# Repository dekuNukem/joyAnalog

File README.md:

# Custom circuit board for Joycon input automation

joyAnalog is a custom board with 12 analog switches and 2 12-bit DAC channels. Its main purpose is for automating Nintendo Switch Joycon inputs, and maybe TAS as well. 

joyAnalog presents itself to PC as a virtual USB serial port, so no special drivers are needed. Simply connect the button and joystick test points to the headers to allow the Joycon be controlled from a PC.

## Specs

* STM32F072C8T6 microcontroller, 16KB RAM, 64KB ROM
* 2x ADG714 SPI analog switch
* 1KB I2C EEPROM
* Automatic power switching
* User LED and button

## Header mappings

See [this PDF](datasheets/header_mapping.pdf).

## Twitch Plays Nintendo Switch

I dug up and reused a portion of my old code for TwitchPlaysPokemonX, [see here](./TwitchPlaysNintendoSwitch).

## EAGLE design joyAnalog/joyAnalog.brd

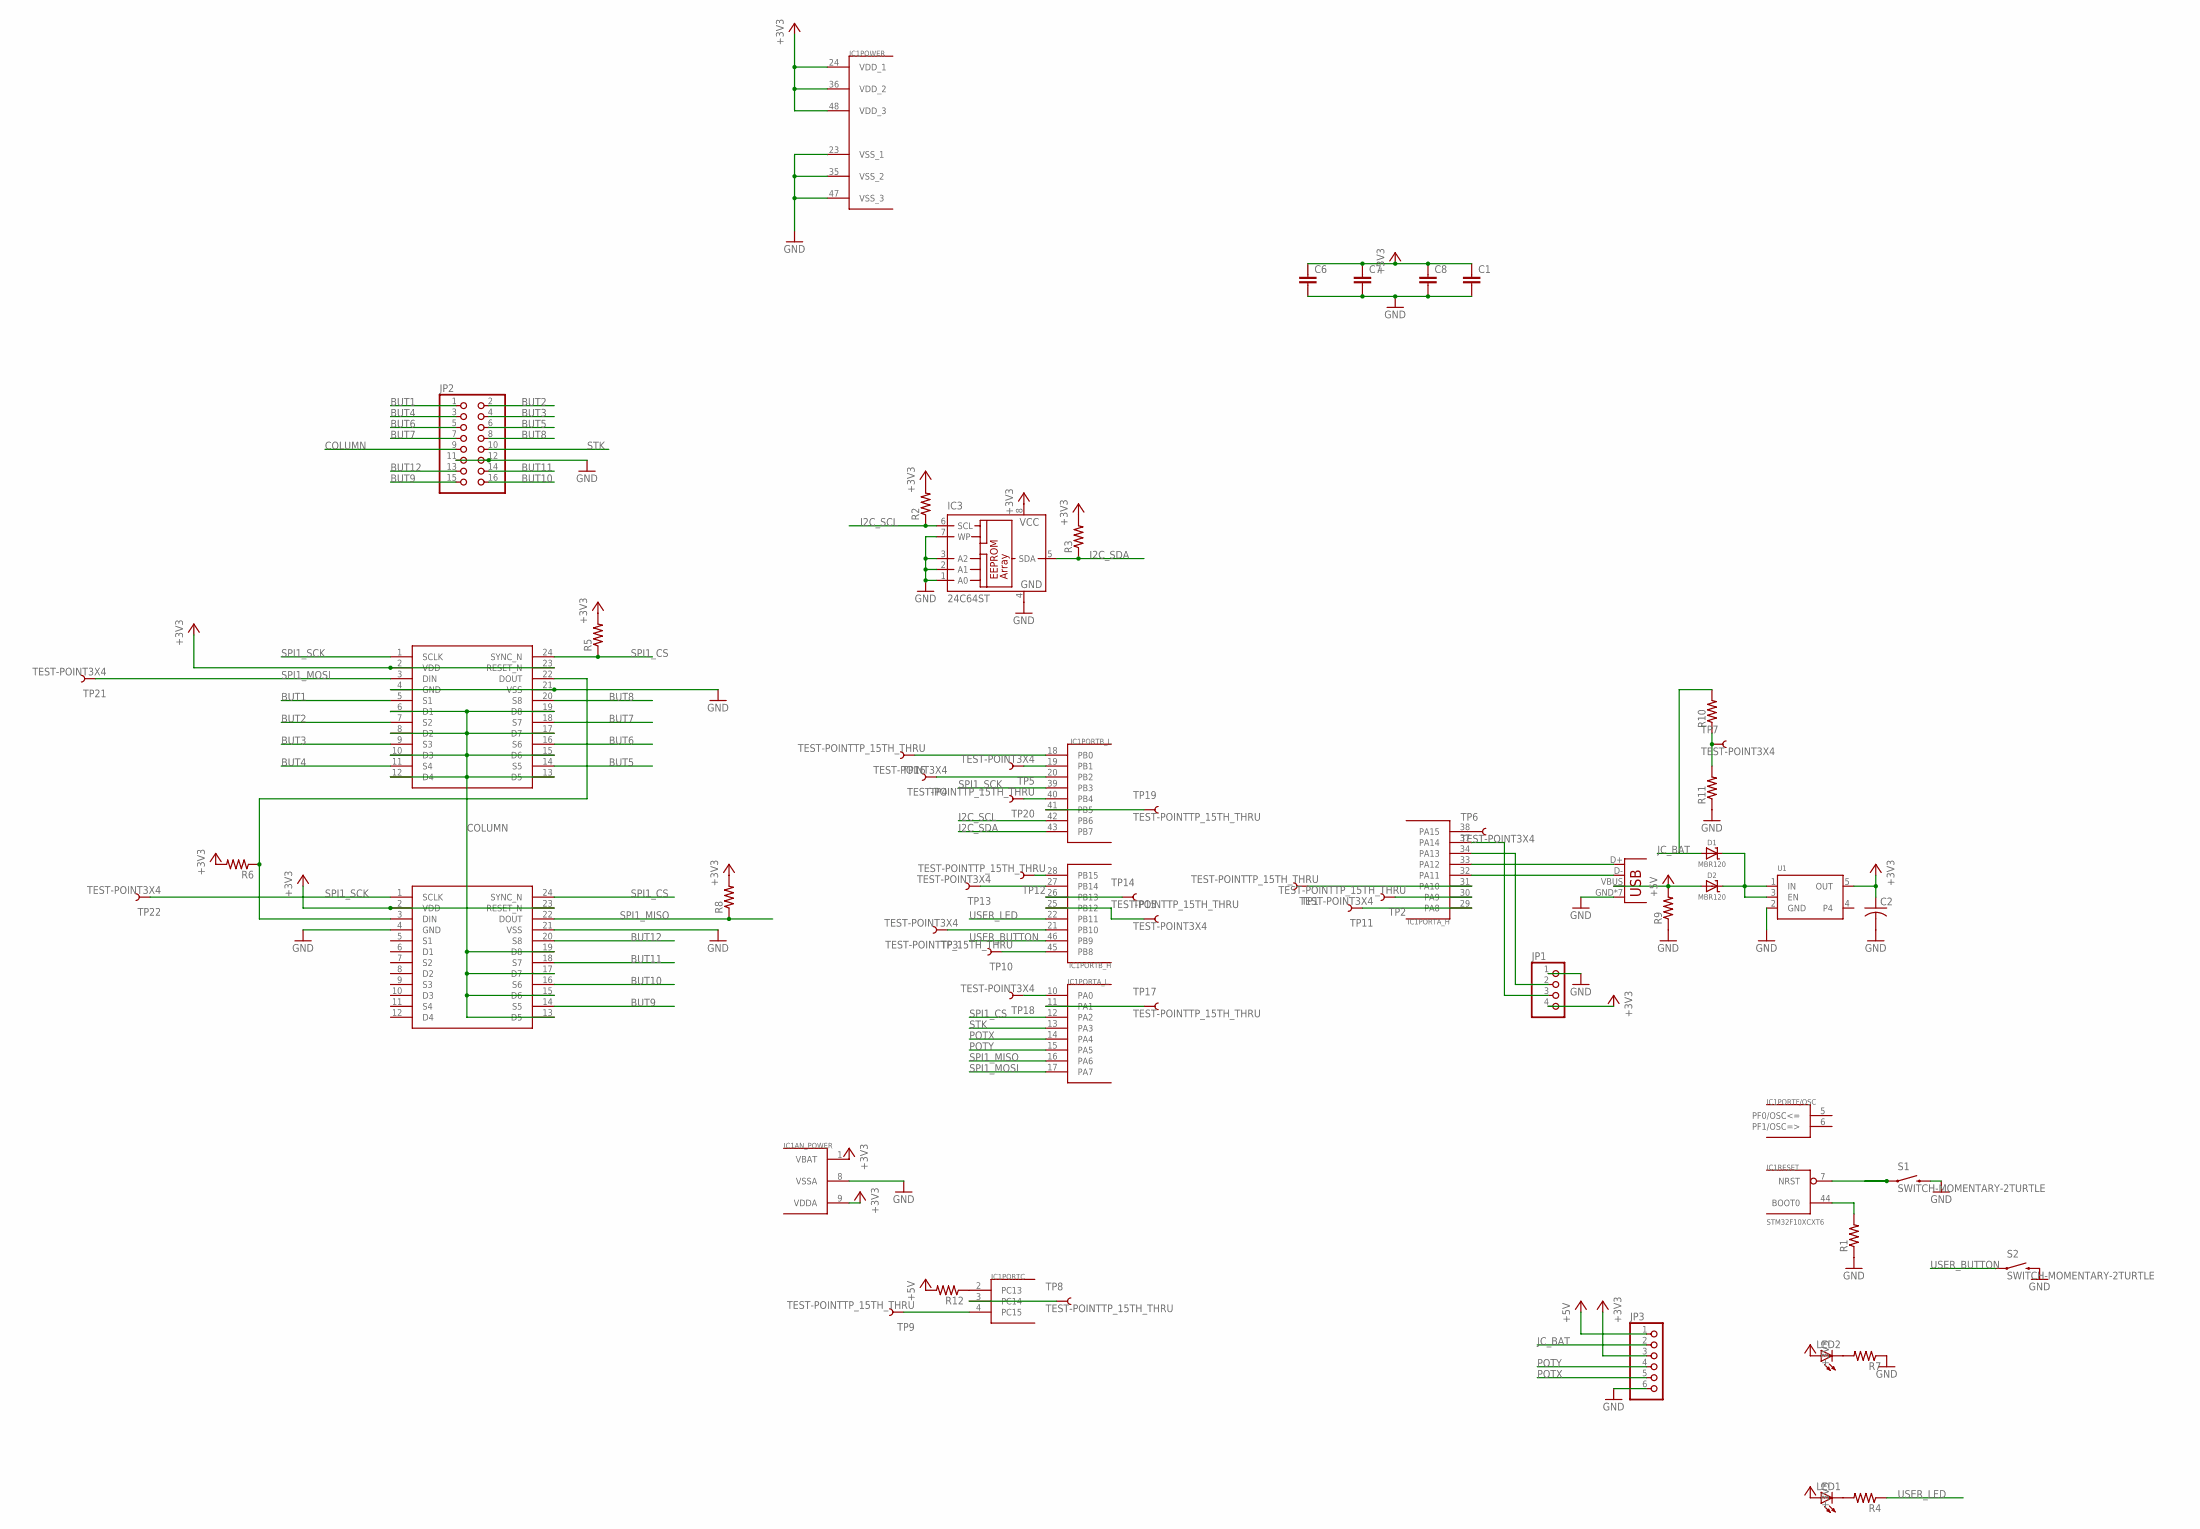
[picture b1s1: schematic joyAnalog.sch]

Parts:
C1, C6, C7, C8: CAP0805; 0805
C2: C-USC1210; C1210
D1, D2: MBR120; SOD-123
IC1: STM32F10XCXT6; TQFP48
IC3: 24C64ST; TSSOP8
JP1: PINHD-1X4; 1X04
JP2: PINHD-2X8; 2X08
JP3: PINHD-1X6CB; 1X06-CLEANBIG
LED1, LED2: LEDCHIP-LED0805; CHIP-LED0805
R1, R2, R3, R4, R5, R6, R7, R8, R9, R10, R11, R12: RESISTOR0805-RES; 0805
S1, S2: SWITCH-MOMENTARY-2TURTLE; KMR2
TP1, TP2, TP8, TP9, TP10, TP12, TP14, TP16, TP17, TP19, TP20: TEST-POINTTP_15TH_THRU; TP_15TH
TP3, TP4, TP5, TP6, TP7, TP11, TP13, TP15, TP18, TP21, TP22: TEST-POINT3X4; PAD.03X.04
U1: VREG_SOT23-5; SOT23-5
U$3, U$4: ADG714_DEV; TSSOP-24
X1: USB-MICROB

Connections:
+3V3: C1.1, C2.1, C6.1, C7.1, C8.1, IC1.1 (VBAT), IC1.9 (VDDA), IC1.24 (VDD_1), IC1.36 (VDD_2), IC1.48 (VDD_3), IC3.8 (VCC), JP1.4, JP3.3, LED1.A, LED2.A, R2.2, R3.2, R5.2, R6.2, R8.2, U1.5 (OUT), U$3.2 (VDD), U$3.23 (RESET_N), U$4.2 (VDD), U$4.23 (RESET_N)
+5V: D2.A, JP3.1, R9.2, R12.2, X1.VBUS
BUT1: JP2.1, U$3.5 (S1)
BUT2: JP2.2, U$3.7 (S2)
BUT3: JP2.4, U$3.9 (S3)
BUT4: JP2.3, U$3.11 (S4)
BUT5: JP2.6, U$3.14 (S5)
BUT6: JP2.5, U$3.16 (S6)
BUT7: JP2.7, U$3.18 (S7)
BUT8: JP2.8, U$3.20 (S8)
BUT9: JP2.15, U$4.14 (S5)
BUT10: JP2.16, U$4.16 (S6)
BUT11: JP2.14, U$4.18 (S7)
BUT12: JP2.13, U$4.20 (S8)
COLUMN: JP2.9, U$3.6 (D1), U$3.8 (D2), U$3.10 (D3), U$3.12 (D4), U$3.13 (D5), U$3.15 (D6), U$3.17 (D7), U$3.19 (D8), U$4.13 (D5), U$4.15 (D6), U$4.17 (D7), U$4.19 (D8)
GND: C1.2, C2.2, C6.2, C7.2, C8.2, IC1.8 (VSSA), IC1.23 (VSS_1), IC1.35 (VSS_2), IC1.47 (VSS_3), IC3.1 (A0), IC3.2 (A1), IC3.3 (A2), IC3.4 (GND), IC3.7 (WP), JP1.1, JP2.11, JP2.12, JP3.6, R1.1, R7.1, R9.1, R11.1, S1.3 (2), S2.3 (2), U1.2 (GND), U$3.4 (GND), U$3.21 (VSS), U$4.4 (GND), U$4.21 (VSS), X1.GND, X1.P1 (GND), X1.P2 (GND), X1.P3 (GND), X1.P4 (GND), X1.P5 (GND), X1.P6 (GND)
I2C_SCL: IC1.42 (PB6), IC3.6 (SCL), R2.1
I2C_SDA: IC1.43 (PB7), IC3.5 (SDA), R3.1
JC_BAT: D1.A, JP3.2, R10.2
unnamed: IC1.7 (NRST), S1.1
unnamed: IC1.44 (BOOT0), R1.2
unnamed: LED1.C, R4.2
unnamed: IC1.33 (PA12), X1.D+
unnamed: R6.1, U$3.22 (DOUT), U$4.3 (DIN)
unnamed: IC1.30 (PA9), TP2.P$1
unnamed: IC1.32 (PA11), X1.D-
unnamed: IC1.34 (PA13), JP1.2
unnamed: IC1.37 (PA14), JP1.3
unnamed: IC1.31 (PA10), TP1.P$1
unnamed: IC1.20 (PB2), TP4.P$1
unnamed: IC1.19 (PB1), TP5.P$1
unnamed: IC1.21 (PB10), TP3.P$1
unnamed: IC1.38 (PA15), TP6.P$1
unnamed: R10.1, R11.2, TP7.P$1
unnamed: IC1.3 (PC14), TP8.P$1
unnamed: IC1.4 (PC15), TP9.P$1
unnamed: IC1.45 (PB8), TP10.P$1
unnamed: IC1.29 (PA8), TP11.P$1
unnamed: IC1.28 (PB15), TP12.P$1
unnamed: IC1.27 (PB14), TP13.P$1
unnamed: IC1.26 (PB13), TP14.P$1
unnamed: IC1.25 (PB12), TP15.P$1
unnamed: IC1.18 (PB0), TP16.P$1
unnamed: IC1.10 (PA0), TP18.P$1
unnamed: IC1.11 (PA1), TP17.P$1
unnamed: IC1.40 (PB4), TP20.P$1
unnamed: IC1.41 (PB5), TP19.P$1
unnamed: LED2.C, R7.2
unnamed: IC1.2 (PC13), R12.1
unnamed: D1.C, D2.C, U1.1 (IN), U1.3 (EN)
POTX: IC1.14 (PA4), JP3.5
POTY: IC1.15 (PA5), JP3.4
SPI1_CS: IC1.12 (PA2), R5.1, U$3.24 (SYNC_N), U$4.24 (SYNC_N)
SPI1_MISO: IC1.16 (PA6), R8.1, U$4.22 (DOUT)
SPI1_MOSI: IC1.17 (PA7), TP21.P$1, U$3.3 (DIN)
SPI1_SCK: IC1.39 (PB3), TP22.P$1, U$3.1 (SCLK), U$4.1 (SCLK)
STK: IC1.13 (PA3), JP2.10
USER_BUTTON: IC1.46 (PB9), S2.1
USER_LED: IC1.22 (PB11), R4.1

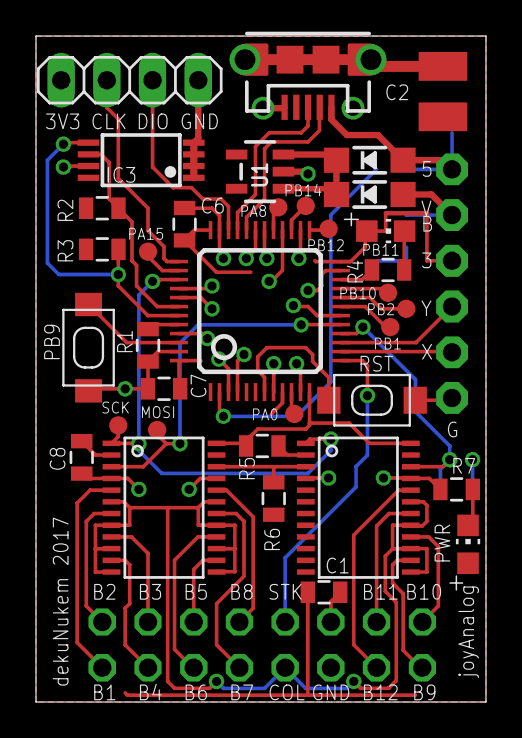
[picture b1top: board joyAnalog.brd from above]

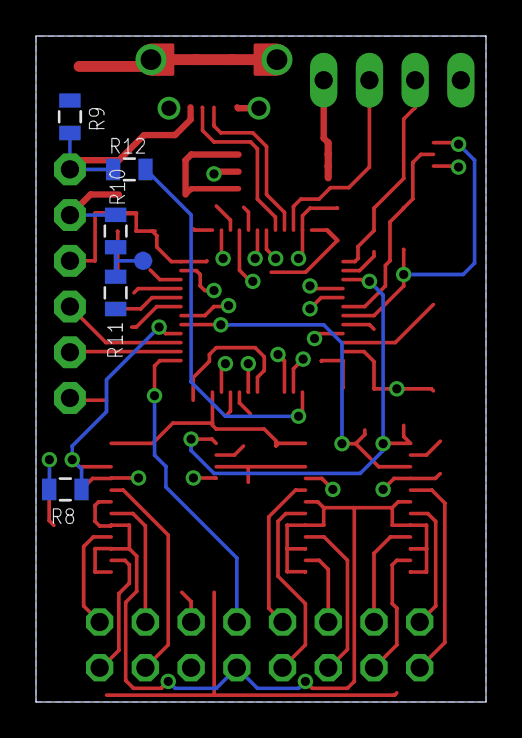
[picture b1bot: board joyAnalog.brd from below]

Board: 2 copper layers, 25.0 x 37.0 mm, 54 parts (6 on the bottom side), 59 nets.

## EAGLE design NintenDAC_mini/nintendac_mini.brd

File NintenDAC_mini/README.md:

## NintenDAC mini

This is the board that's to be used on modifying the Joycon. It's small enough to be taped to the back of each one.

* 48MHz STM32F072C8T6 microcontroller, 64KB flash, 16KB RAM.
* Built-in 2-channel 12-bit DAC.
* 1KB I2C EEPROM, user button, user LED.
* 28 GPIOs(or 32 using internal oscillators), BOOT0, RESET, VBAT, and SWD.
* USB for power and communication, standby wakeup on USB connection.
* Board size 2.5 x 4.1 cm, 1 x 1.6 inch.

## Command protocol

NintenDAC mini uses a simple serial command protocol. To use it open the port at any baud rate, then send a command in ASCII string. The board will send a response back.

Commands should be in lower case, and end with a single `\n`.

### Commands

**command**|**arguments**|**remark**|**response**|**example**
:-----:|:-----:|:-----:|:-----:|:-----:
`eepinit`|none|initializes EEPROM to default value|`eepinit OK`|`eepinit`
`settype`|l / r|set this board as left or right Joycon|`settype OK`|`settype l`
`whoami`|none|see which side is this board|A string containing `LEFT` or `RIGHT`; `unknown` if incorrectly set up|`whoami`
`bh`|button args (see below)|hold button|`bh OK` if no error; `ERROR`  otherwise|`bh a b x`
`br`|button args (see below)|release button|`br OK` if no error; `ERROR` otherwise|`br a b x`
`bra`|none|release all buttons on this board|`bra OK`|`bra`
`sh`|x y|move stick to x and y value. x y should be between 0 and 255 inclusive; 127 is netural position|`bh OK`|`sh 127 245`
`sr`|none|move stick back to netural position|`br OK`|`sr`
`sd`|none|stick disengage|`sd OK`|`sd`
`reset`|none|release all buttons as well as disengage the stick|`reset OK`|`reset`

### Button args

**arg**|**button**
:-----:|:-----:
`du`|D-pad up
`dd`|D-pad down
`dl`|D-pad left
`dr`|D-pad right
`ls`|L button
`zl`|ZL button
`-`|minus button 
`cap`|capture button
`lsl`|left Joycon SL button
`lsr`|left Joycon SR button
`syncl`|left Joycon SYNC button
`sbl`|left Joycon stick button
`a`|A button
`b`|B button
`x`|X button
`y`|Y button
`rs`|R button
`zr`|ZR button
`+`|plus button
`h`|home button
`rsl`|right Joycon SL button
`rsr`|right Joycon SR button
`syncr`|right Joycon SYNC button
`sbr`|right Joycon stick button

### A few words about commands

* `sh` and `sr` will take over the control stick, meaning the input won't change when you move the stick with your finger when those commands are active. To get back to manual control use `sd`

* Not all buttons are available on one board. For example if you try to `bh a` on a left Joycon board, you will get an error because there is no A button on left Joycon.

* `bh` and `br` can have one or multiple arguments, as long as they are all valid. So you can have `bh a` or `bh a b x y zr h +` etc. The max number of arguments is 16.

## NintenDAC Python3 library

I also wrote a [python3 library](./pythonlib) so you don't have to remember all the commands above. It requires `pyserial`.

A simple example:

```
import ndacmini

switch = ndacmini.ndacmini("COM5", "COM6")
switch.connect()

switch.button_hold(['a', 'b', 'zl', 'zr'])
switch.stick_hold('l', 64, 192)
switch.reset()
switch.disconnect()

```

A more detailed example with comments can be found [here](./pythonlib/example.py)

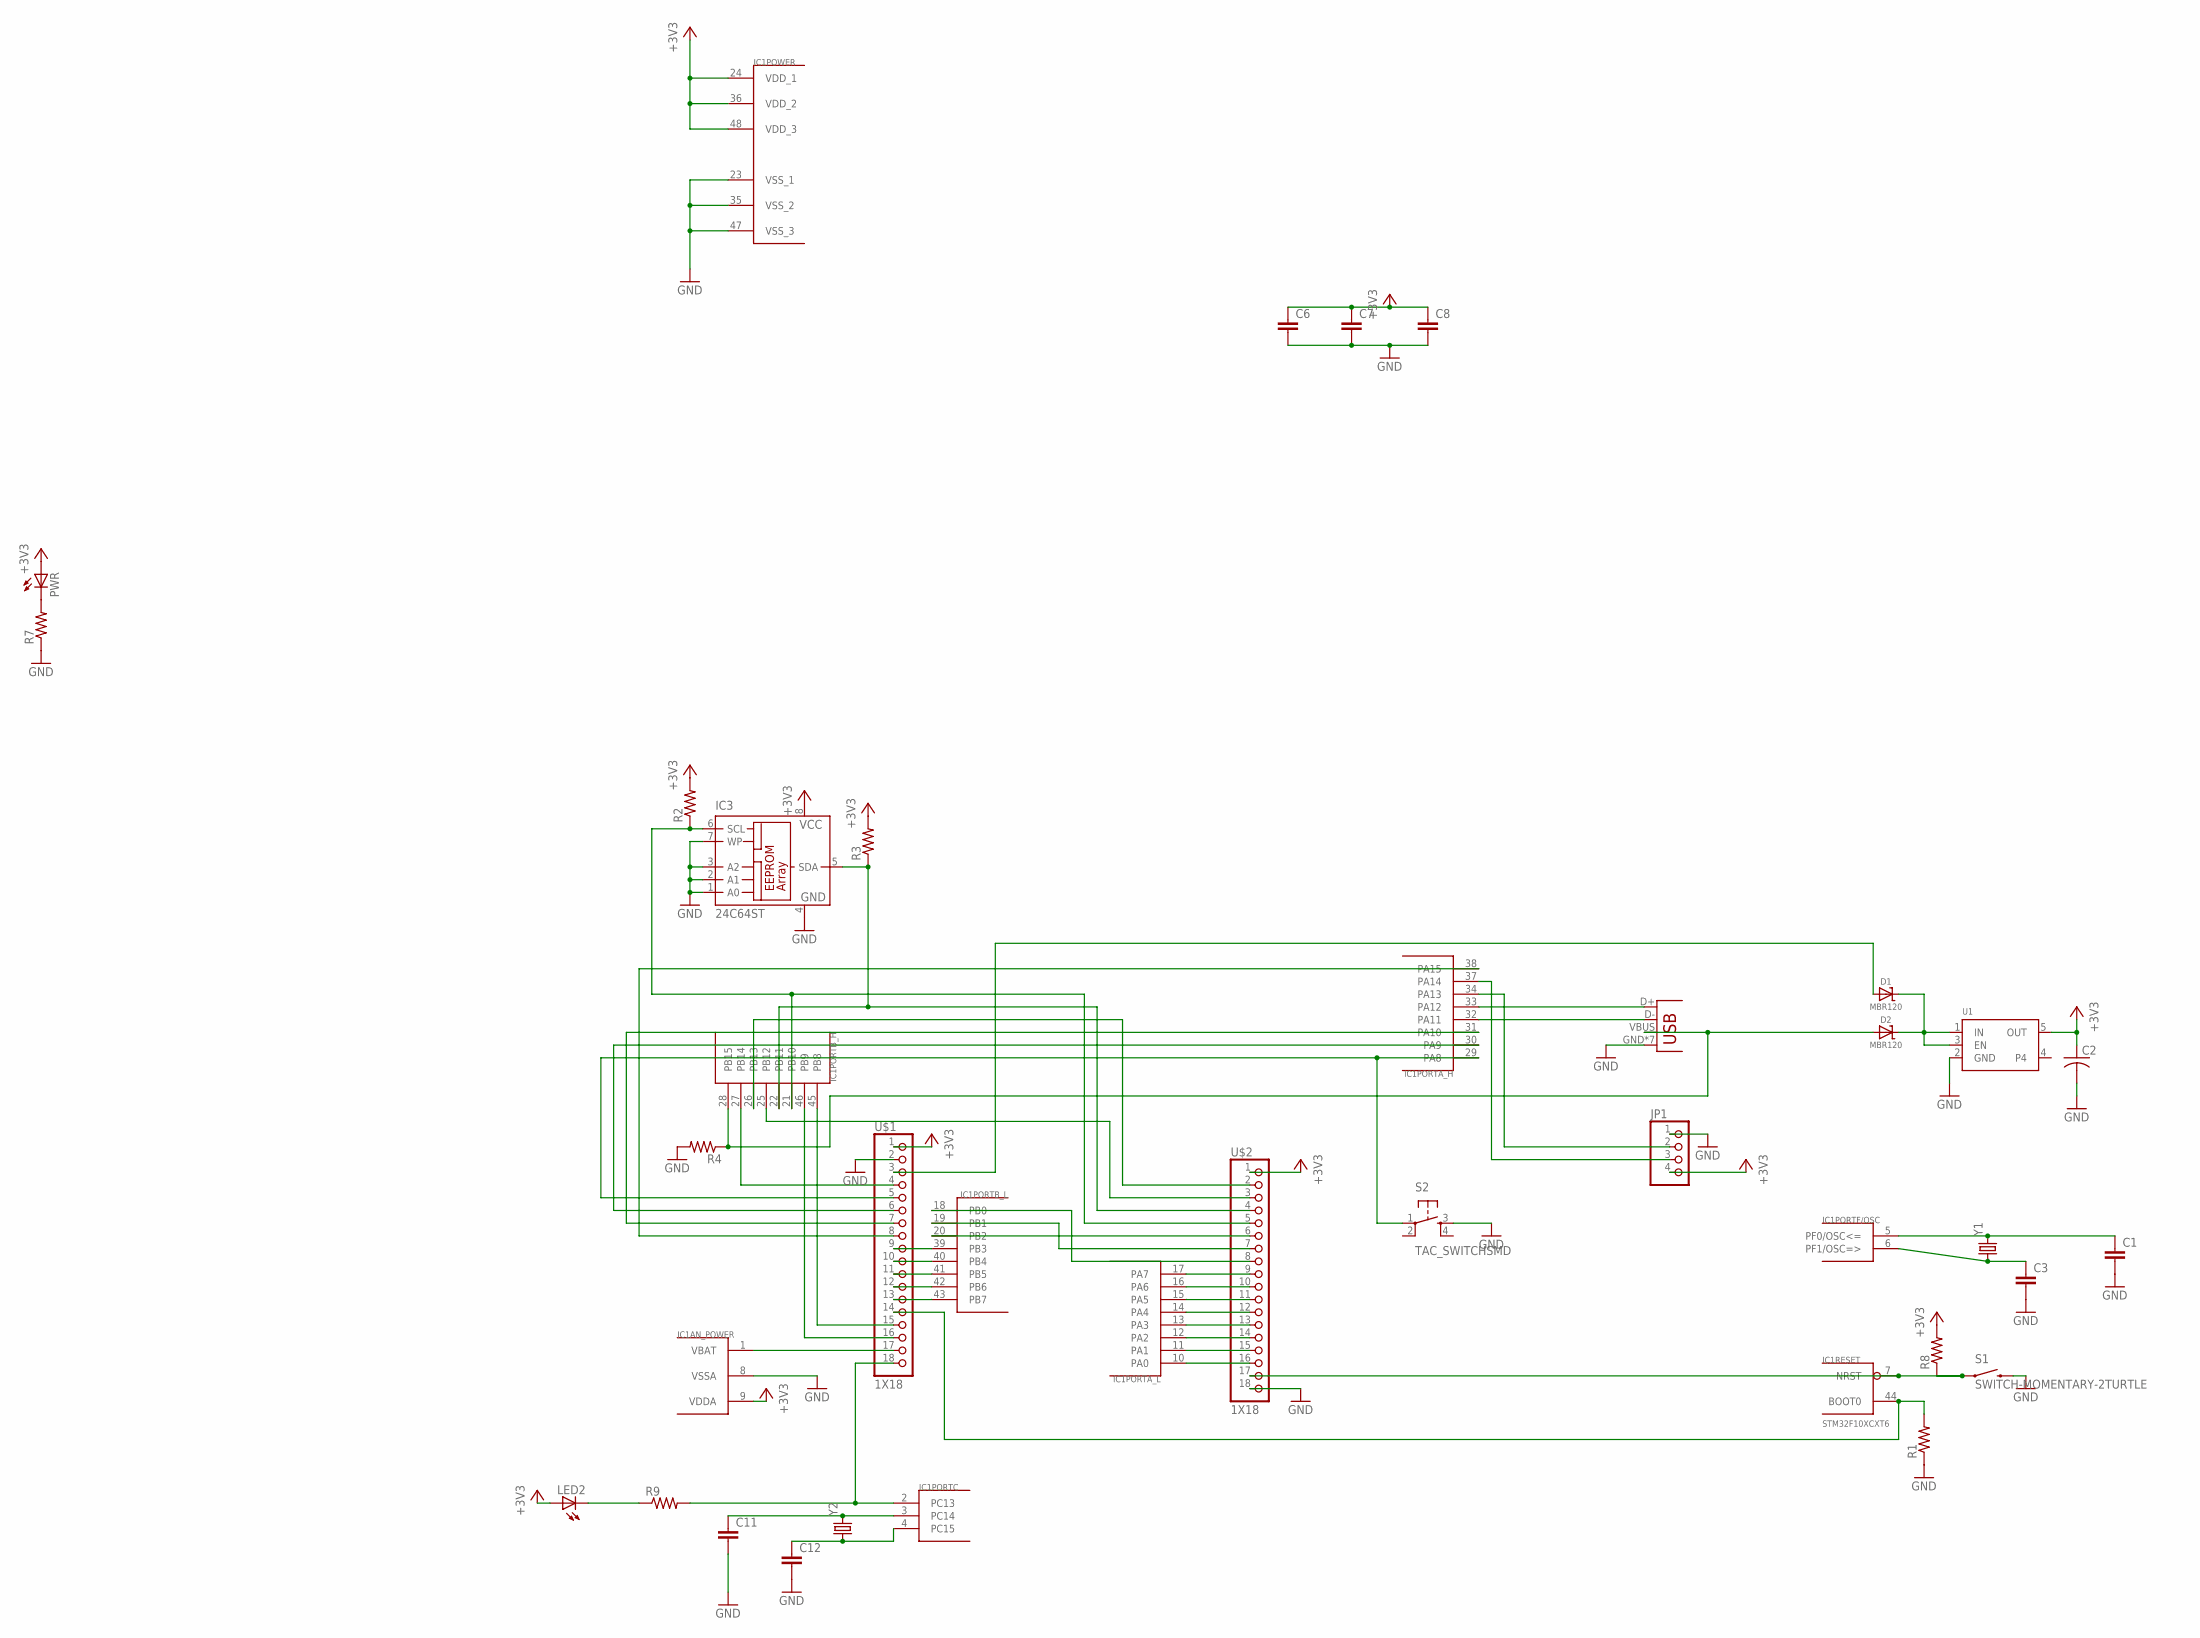
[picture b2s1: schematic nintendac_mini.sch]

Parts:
C1, C3, C6, C7, C8, C11, C12: CAP0805; 0805
C2: C-USC1210; C1210
D1, D2: MBR120; SOD-123
IC1: STM32F10XCXT6; TQFP48
IC3: 24C64ST; TSSOP8
JP1: PINHD-1X4; 1X04
LED2: LEDCHIP-LED0805; CHIP-LED0805
PWR: LEDCHIP-LED0805; CHIP-LED0805
R1, R2, R3, R4, R7, R8, R9: RESISTOR0805-RES; 0805
S1: SWITCH-MOMENTARY-2TURTLE; KMR2
S2: TAC_SWITCHSMD; TACTILE-SWITCH-SMD
U1: VREG_SOT23-5; SOT23-5
U$1, U$2: 1X18
X1: USB-MICROB
Y1: CRYSTALHC49US; HC49US
Y2: CRYSTALTC26H_EZ; TC26HEZ

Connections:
+3V3: C2.1, C6.1, C7.1, C8.1, IC1.9 (VDDA), IC1.24 (VDD_1), IC1.36 (VDD_2), IC1.48 (VDD_3), IC3.8 (VCC), JP1.4, LED2.A, PWR.A, R2.2, R3.2, R8.2, U1.5 (OUT), U$1.1, U$2.1
GND: C1.2, C2.2, C3.2, C6.2, C7.2, C8.2, C11.2, C12.2, IC1.8 (VSSA), IC1.23 (VSS_1), IC1.35 (VSS_2), IC1.47 (VSS_3), IC3.1 (A0), IC3.2 (A1), IC3.3 (A2), IC3.4 (GND), IC3.7 (WP), JP1.1, R1.1, R4.2, R7.1, S1.3 (2), S2.3, U1.2 (GND), U$1.2, U$2.18, X1.GND, X1.P1 (GND), X1.P2 (GND), X1.P3 (GND), X1.P4 (GND), X1.P5 (GND), X1.P6 (GND)
unnamed: IC1.7 (NRST), R8.1, S1.1, U$2.17
unnamed: D1.A, U$1.3
unnamed: IC1.44 (BOOT0), R1.2, U$1.14
unnamed: IC1.33 (PA12), X1.D+
unnamed: C1.1, IC1.5 (PF0/OSC<=), Y1.2
unnamed: C3.1, IC1.6 (PF1/OSC=>), Y1.1
unnamed: IC1.32 (PA11), X1.D-
unnamed: IC1.34 (PA13), JP1.2
unnamed: IC1.37 (PA14), JP1.3
unnamed: IC1.10 (PA0), U$2.16
unnamed: IC1.11 (PA1), U$2.15
unnamed: IC1.12 (PA2), U$2.14
unnamed: IC1.13 (PA3), U$2.13
unnamed: IC1.14 (PA4), U$2.12
unnamed: IC1.15 (PA5), U$2.11
unnamed: IC1.16 (PA6), U$2.10
unnamed: IC1.17 (PA7), U$2.9
unnamed: IC1.21 (PB10), IC3.6 (SCL), R2.1, U$2.5
unnamed: IC1.22 (PB11), IC3.5 (SDA), R3.1, U$2.4
unnamed: IC1.18 (PB0), U$2.8
unnamed: IC1.19 (PB1), U$2.7
unnamed: IC1.20 (PB2), U$2.6
unnamed: IC1.43 (PB7), U$1.13
unnamed: IC1.42 (PB6), U$1.12
unnamed: IC1.41 (PB5), U$1.11
unnamed: IC1.40 (PB4), U$1.10
unnamed: PWR.C, R7.2
unnamed: C11.1, IC1.3 (PC14), Y2.2
unnamed: C12.1, IC1.4 (PC15), Y2.1
unnamed: IC1.39 (PB3), U$1.9
unnamed: D1.C, D2.C, U1.1 (IN), U1.3 (EN)
unnamed: IC1.2 (PC13), R9.2, U$1.18
unnamed: IC1.1 (VBAT), U$1.17
unnamed: IC1.46 (PB9), U$1.16
unnamed: IC1.45 (PB8), U$1.15
unnamed: IC1.25 (PB12), U$2.3
unnamed: IC1.26 (PB13), U$2.2
unnamed: IC1.38 (PA15), U$1.8
unnamed: IC1.31 (PA10), U$1.7
unnamed: IC1.30 (PA9), U$1.6
unnamed: IC1.29 (PA8), S2.1, U$1.5
unnamed: IC1.27 (PB14), U$1.4
unnamed: D2.A, IC1.28 (PB15), R4.1, X1.VBUS
unnamed: LED2.C, R9.1

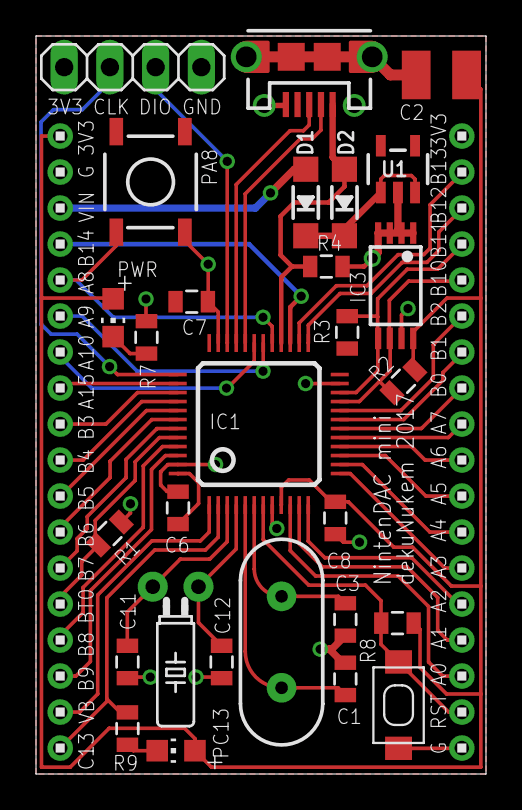
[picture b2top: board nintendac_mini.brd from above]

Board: 2 copper layers, 25.0 x 41.0 mm, 30 parts (0 on the bottom side), 46 nets.

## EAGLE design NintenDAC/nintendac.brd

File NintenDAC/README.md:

## NintenDAC

This is the bigger board that could be used on modifying the pro controller, or the console itself. It has more GPIOs than the mini, and has 10 channels of high speed DAC output.

* 48MHz STM32F072R8T6 microcontroller, 64KB flash, 16KB RAM.
* MAX5723/MAX5724/MAX5725 8-channel high-speed SPI DAC + 2-channel built-in DAC.
* 1KB I2C EEPROM, user button, user LED.
* 36 GPIOs(or 40 using internal oscillators), BOOT0, RESET, VBAT, and SWD.
* USB for power and communication, standby wakeup on USB connection.
* Board size 4.1 x 4.1 cm, or 1.65 x 1.65 inch.

## Command protocol

NintenDAC uses a simple serial command protocol. To use it open the port at any baud rate, then send a command in ASCII string. The board will send a respond back.

Commands should be in lower case, and end with a single `\n`.

### Commands

**command**|**arguments**|**remark**|**response**|**example**
:-----:|:-----:|:-----:|:-----:|:-----:
`eepinit`|none|initializes EEPROM to default value|`eepinit OK`|`eepinit`
`settype`|l / r|set this board as left or right Joycon|`settype OK`|`settype l`
`whoami`|none|see which side is this board|A string containing `LEFT` or `RIGHT`; `unknown` if incorrectly set up|`whoami`
`bh`|button args (see below)|hold button|`bh OK` if no error; `ERROR`  otherwise|`bh a b x`
`br`|button args (see below)|release button|`br OK` if no error; `ERROR` otherwise|`br a b x`
`bra`|none|release all buttons on this board|`bra OK`|`bra`
`reset`|none|release all buttons as well as disengage the stick|`reset OK`|`reset`

---under construction---under construction---

### Button args

**arg**|**button**
:-----:|:-----:
`du`|D-pad up
`dd`|D-pad down
`dl`|D-pad left
`dr`|D-pad right
`ls`|L button
`zl`|ZL button
`-`|minus button 
`cap`|capture button
`sbl`|left stick button
`a`|A button
`b`|B button
`x`|X button
`y`|Y button
`rs`|R button
`zr`|ZR button
`+`|plus button
`h`|home button
`sbr`|right stick button
`sync`|SYNC button

### A few words about commands

* `sh` and `sr` will take over the control stick, meaning the input won't change when you move the stick with your finger when those commands are active. To get back to manual control use `sd`

* `bh` and `br` can have one or multiple arguments, as long as they are all valid. So you can have `bh a` or `bh a b x y zr h +` etc. The max number of arguments is 16.

---under construction---under construction---

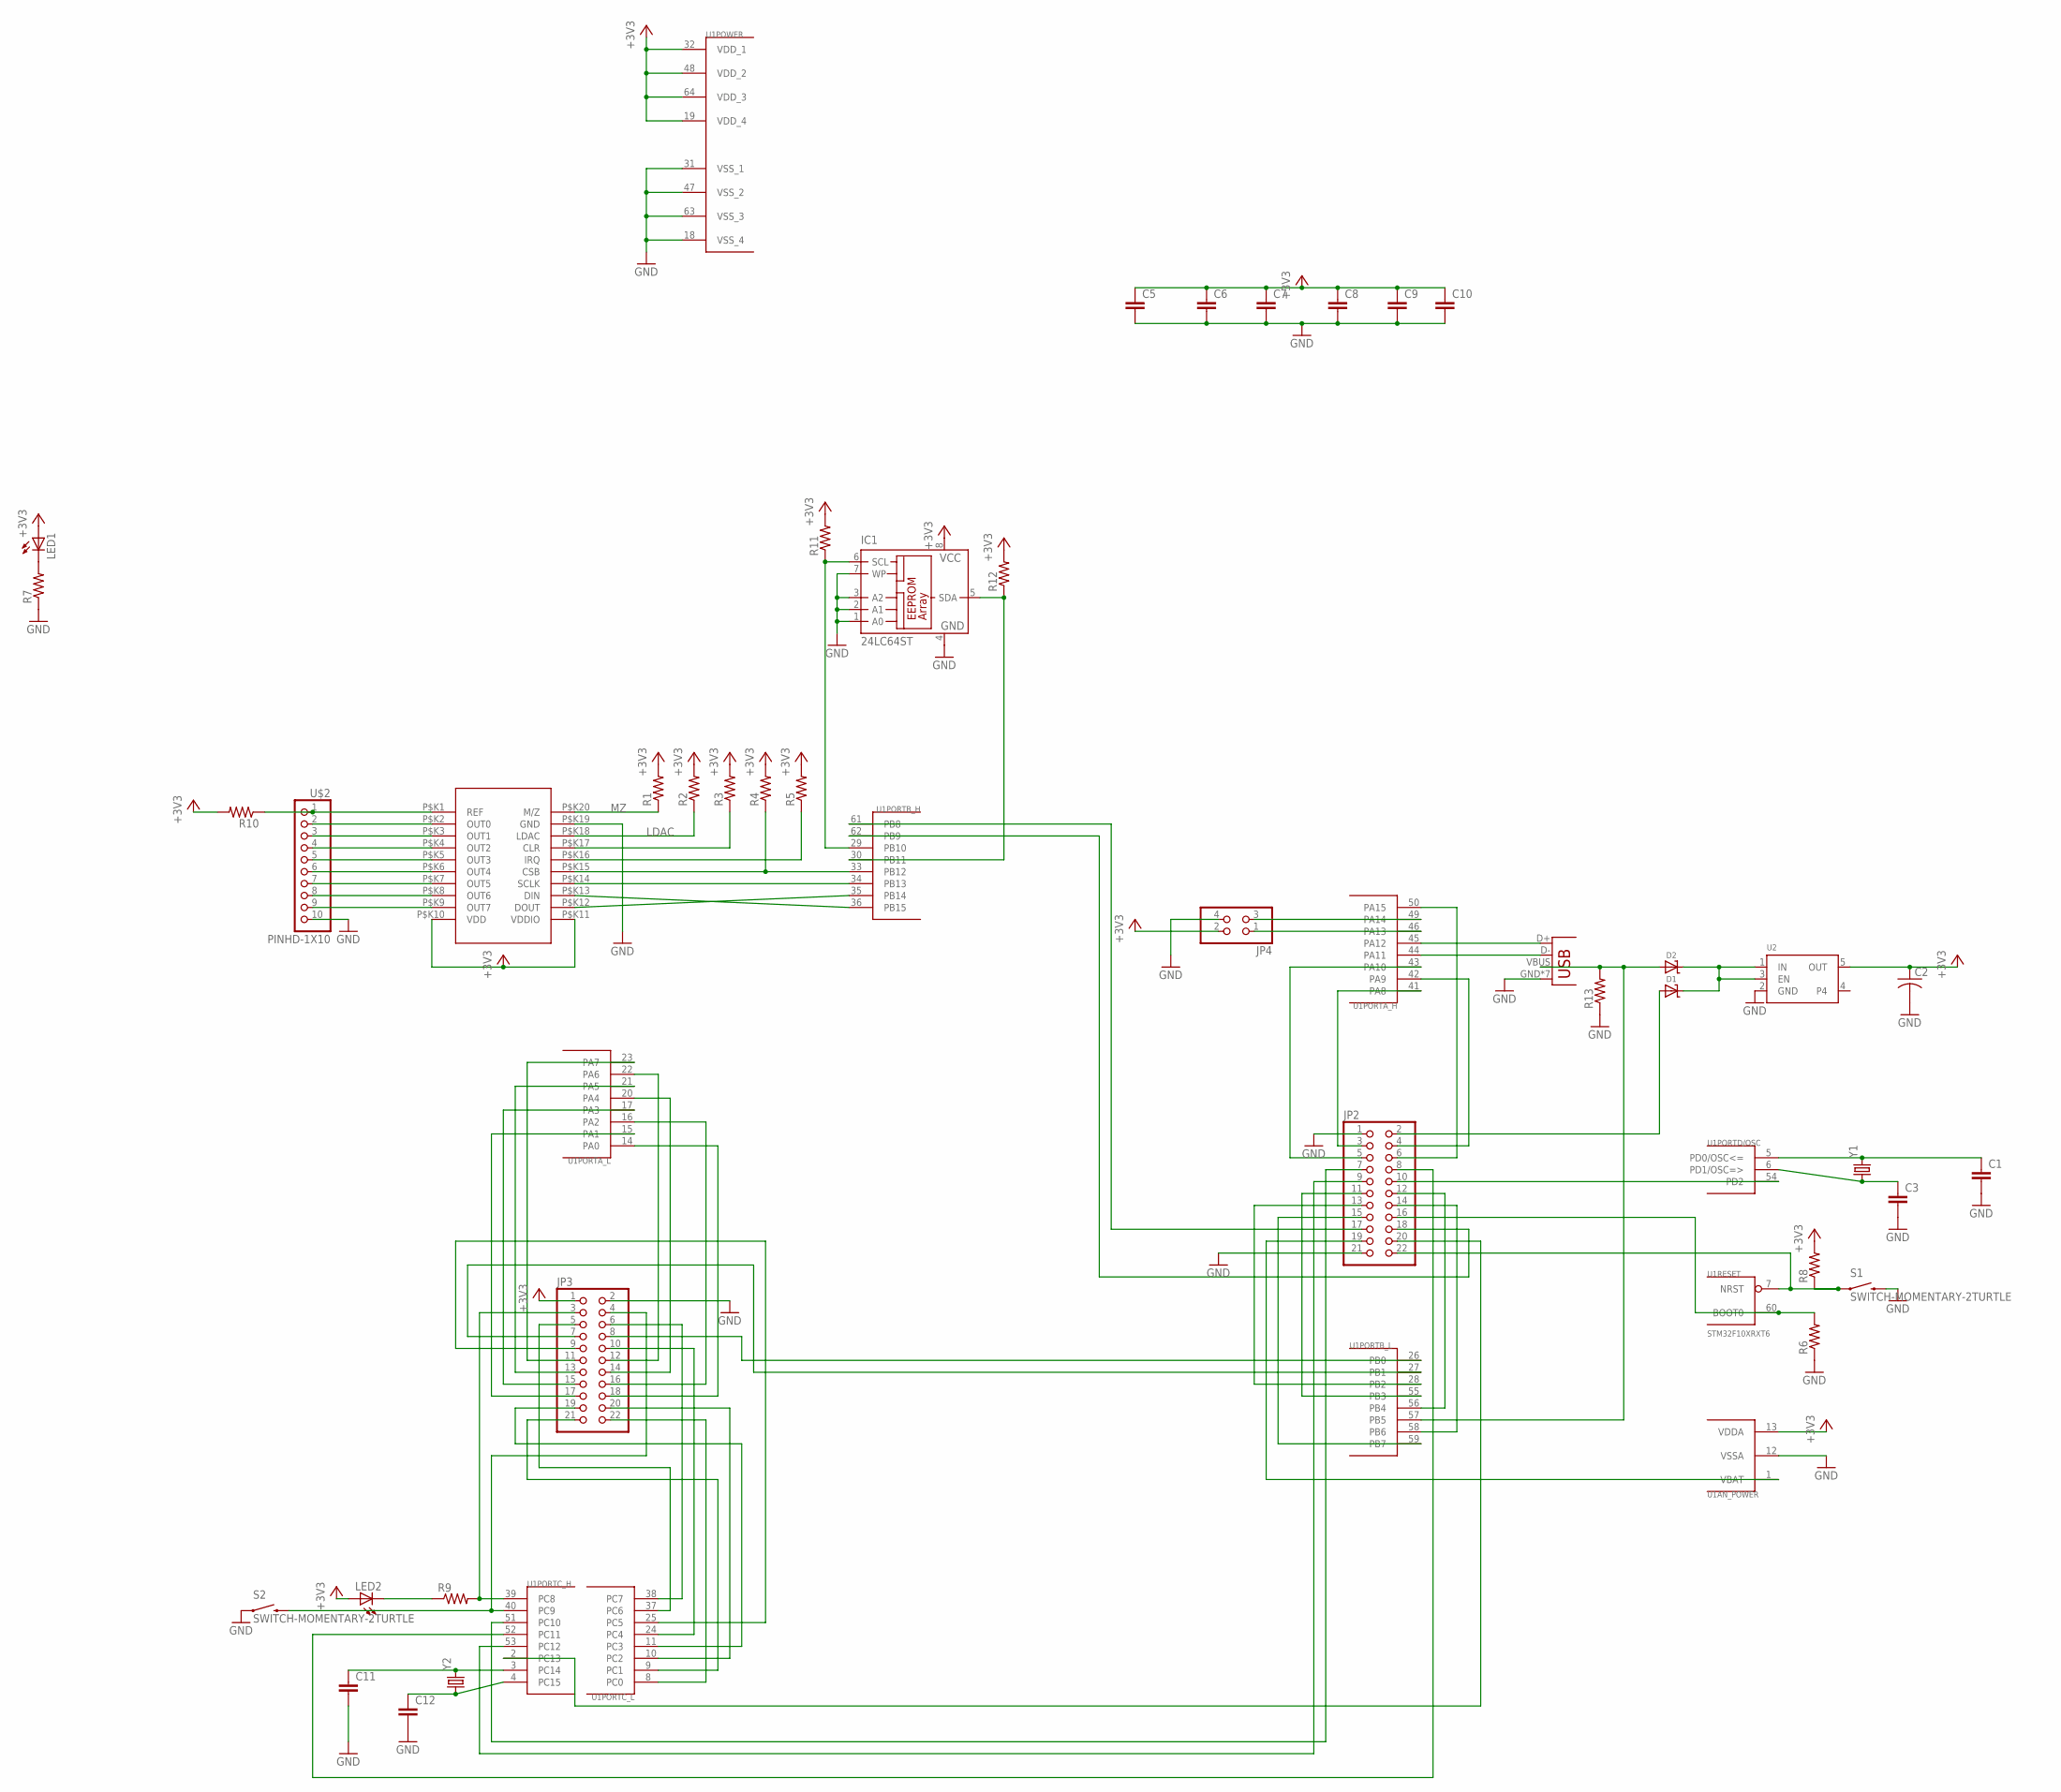
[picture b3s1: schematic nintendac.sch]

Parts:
C1, C3, C5, C6, C7, C8, C9, C10, C11, C12: CAP0805; 0805
C2: C-USC1210; C1210
D1, D2: DIODE-SCHOTTKYSOD-123; SOD-123
IC1: 24LC64ST; TSSOP8
JP2, JP3: PINHD-2X11; 2X11
JP4: PINHD-2X2; 2X02
LED1, LED2: LEDCHIP-LED0805; CHIP-LED0805
R1, R2, R3, R4, R5, R6, R7, R8, R9, R10, R11, R12, R13: RESISTOR0805-RES; 0805
S1, S2: SWITCH-MOMENTARY-2TURTLE; KMR2
U1: STM32F10XRXT6; TQFP64
U2: VREG_SOT23-5; SOT23-5
U$1: MAX572X; TSSOP20
U$2: PINHD-1X10; 1X10-BIG
X1: USB-MICROB
Y1: CRYSTALHC49US; HC49US
Y2: CRYSTALTC26H_EZ; TC26HEZ

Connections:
+3V3: C2.1, C5.1, C6.1, C7.1, C8.1, C9.1, C10.1, IC1.8 (VCC), JP3.1, JP4.2, LED1.A, LED2.A, R1.2, R2.2, R3.2, R4.2, R5.2, R8.2, R10.2, R11.2, R12.2, U1.13 (VDDA), U1.19 (VDD_4), U1.32 (VDD_1), U1.48 (VDD_2), U1.64 (VDD_3), U2.5 (OUT), U$1.P$K10 (VDD), U$1.P$K11 (VDDIO)
GND: C1.2, C2.2, C3.2, C5.2, C6.2, C7.2, C8.2, C9.2, C10.2, C11.2, C12.2, IC1.1 (A0), IC1.2 (A1), IC1.3 (A2), IC1.4 (GND), IC1.7 (WP), JP2.1, JP2.21, JP3.2, JP4.4, R6.1, R7.1, R13.1, S1.3 (2), S2.1, U1.12 (VSSA), U1.18 (VSS_4), U1.31 (VSS_1), U1.47 (VSS_2), U1.63 (VSS_3), U2.2 (GND), U$1.P$K19 (GND), U$2.10, X1.GND, X1.P1 (GND), X1.P2 (GND), X1.P3 (GND), X1.P4 (GND), X1.P5 (GND), X1.P6 (GND)
LDAC: R2.1, U$1.P$K18 (LDAC)
MZ: R1.1, U$1.P$K20 (M/Z)
unnamed: JP2.22, R8.1, S1.1, U1.7 (NRST)
unnamed: D1.C, D2.C, U2.1 (IN), U2.3 (EN)
unnamed: U1.44 (PA11), X1.D-
unnamed: U1.45 (PA12), X1.D+
unnamed: C1.1, U1.5 (PD0/OSC<=), Y1.2
unnamed: C3.1, U1.6 (PD1/OSC=>), Y1.1
unnamed: R10.1, U$1.P$K1 (REF), U$2.1
unnamed: U$1.P$K2 (OUT0), U$2.2
unnamed: U$1.P$K3 (OUT1), U$2.3
unnamed: U$1.P$K4 (OUT2), U$2.4
unnamed: U$1.P$K5 (OUT3), U$2.5
unnamed: U$1.P$K6 (OUT4), U$2.6
unnamed: U$1.P$K7 (OUT5), U$2.7
unnamed: U$1.P$K8 (OUT6), U$2.8
unnamed: U$1.P$K9 (OUT7), U$2.9
unnamed: U1.36 (PB15), U$1.P$K13 (DIN)
unnamed: U1.35 (PB14), U$1.P$K12 (DOUT)
unnamed: U1.34 (PB13), U$1.P$K14 (SCLK)
unnamed: R4.1, U1.33 (PB12), U$1.P$K15 (CSB)
unnamed: R5.1, U$1.P$K16 (IRQ)
unnamed: R3.1, U$1.P$K17 (CLR)
unnamed: JP4.3, U1.49 (PA14)
unnamed: JP3.5, U1.37 (PC6)
unnamed: JP4.1, U1.46 (PA13)
unnamed: JP3.6, U1.38 (PC7)
unnamed: JP2.16, R6.2, U1.60 (BOOT0)
unnamed: LED1.C, R7.2
unnamed: C11.1, U1.3 (PC14), Y2.2
unnamed: C12.1, U1.4 (PC15), Y2.1
unnamed: JP3.4, S2.3 (2), U1.40 (PC9)
unnamed: JP2.3, U1.41 (PA8)
unnamed: JP3.3, R9.2, U1.39 (PC8)
unnamed: JP2.4, U1.42 (PA9)
unnamed: JP2.5, U1.43 (PA10)
unnamed: JP3.7, U1.27 (PB1)
unnamed: JP3.8, U1.26 (PB0)
unnamed: JP3.9, U1.25 (PC5)
unnamed: JP3.10, U1.24 (PC4)
unnamed: JP3.11, U1.23 (PA7)
unnamed: JP3.12, U1.22 (PA6)
unnamed: JP3.13, U1.21 (PA5)
unnamed: JP3.14, U1.20 (PA4)
unnamed: JP3.15, U1.17 (PA3)
unnamed: JP3.16, U1.16 (PA2)
unnamed: JP3.17, U1.15 (PA1)
unnamed: JP3.18, U1.14 (PA0)
unnamed: JP3.22, U1.8 (PC0)
unnamed: JP3.21, U1.9 (PC1)
unnamed: JP3.20, U1.10 (PC2)
unnamed: JP3.19, U1.11 (PC3)
unnamed: JP2.6, U1.50 (PA15)
unnamed: JP2.7, U1.51 (PC10)
unnamed: JP2.9, U1.53 (PC12)
unnamed: JP2.8, U1.52 (PC11)
unnamed: JP2.10, U1.54 (PD2)
unnamed: JP2.11, U1.55 (PB3)
unnamed: JP2.12, U1.56 (PB4)
unnamed: D2.A, R13.2, U1.57 (PB5), X1.VBUS
unnamed: JP2.14, U1.58 (PB6)
unnamed: JP2.15, U1.59 (PB7)
unnamed: JP2.17, U1.61 (PB8)
unnamed: JP2.18, U1.62 (PB9)
unnamed: JP2.19, U1.1 (VBAT)
unnamed: JP2.20, U1.2 (PC13)
unnamed: LED2.C, R9.1
unnamed: D1.A, JP2.2
unnamed: IC1.6 (SCL), R11.1, U1.29 (PB10)
unnamed: IC1.5 (SDA), R12.1, U1.30 (PB11)
unnamed: JP2.13, U1.28 (PB2)

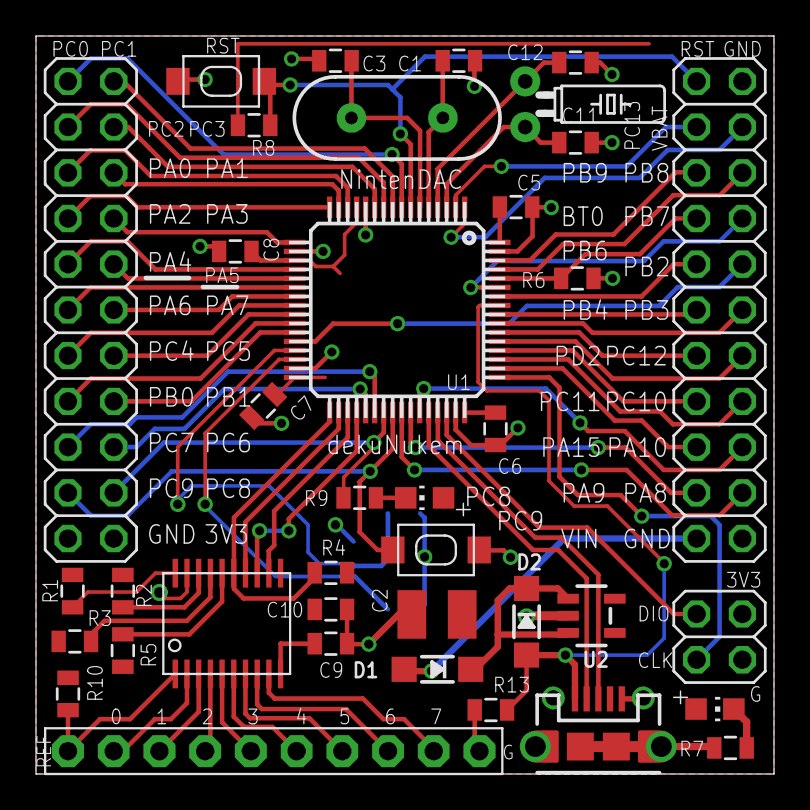
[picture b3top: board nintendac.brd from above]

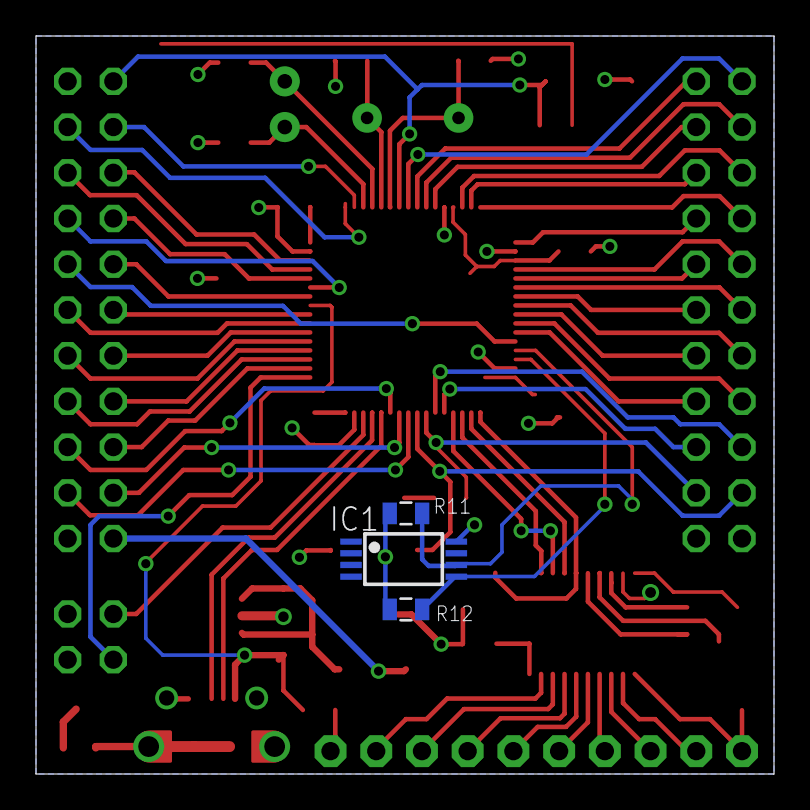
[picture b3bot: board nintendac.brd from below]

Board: 2 copper layers, 41.0 x 41.0 mm, 41 parts (3 on the bottom side), 73 nets.

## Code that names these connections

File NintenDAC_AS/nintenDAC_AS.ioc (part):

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Mcu.Name=STM32F072C(8-B)Tx
Mcu.Package=LQFP48
Mcu.UserName=STM32F072C8Tx
PA10.Mode=Asynchronous
PA10.Signal=USART1_RX
PA11.Mode=Device
PA11.Signal=USB_DM
PA12.Mode=Device
PA12.Signal=USB_DP
PA13.Mode=Serial_Wire
PA13.Signal=SYS_SWDIO
PA14.Mode=Serial_Wire
PA14.Signal=SYS_SWCLK
PA2.GPIOParameters=GPIO_Label
PA2.GPIO_Label=SPI1_CS
PA2.Signal=GPIO_Output
PA4.Signal=COMP_DAC1_group
PA5.Signal=COMP_DAC2_group
PA6.GPIOParameters=GPIO_PuPd
PA6.GPIO_PuPd=GPIO_PULLUP
PA6.Mode=Full_Duplex_Master
PA6.Signal=SPI1_MISO
PA7.Mode=Full_Duplex_Master
PA7.Signal=SPI1_MOSI
PA9.Mode=Asynchronous
PA9.Signal=USART1_TX
PB11.GPIOParameters=GPIO_Label
PB11.GPIO_Label=USER_LED
PB11.Signal=GPIO_Output
PB3.Mode=Full_Duplex_Master
PB3.Signal=SPI1_SCK
PB6.Mode=I2C
PB6.Signal=I2C1_SCL
PB7.Mode=I2C
PB7.Signal=I2C1_SDA
PB9.GPIOParameters=GPIO_Label
PB9.GPIO_Label=USER_BUTTON
PB9.Signal=GPIO_Input
RCC.HSEState=RCC_HSE_OFF
RCC.SYSCLKFreq_VALUE=48000000
RCC.SYSCLKSource=RCC_SYSCLKSOURCE_PLLCLK

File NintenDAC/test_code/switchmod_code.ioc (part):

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Mcu.Name=STM32F072R(8-B)Tx
Mcu.Package=LQFP64
Mcu.UserName=STM32F072R8Tx
PA11.Mode=Device
PA11.Signal=USB_DM
PA12.Mode=Device
PA12.Signal=USB_DP
PA13.Mode=Serial_Wire
PA13.Signal=SYS_SWDIO
PA14.Mode=Serial_Wire
PA14.Signal=SYS_SWCLK
PA4.GPIOParameters=GPIO_Label
PA4.GPIO_Label=STM32_DAC_X
PA4.Signal=COMP_DAC1_group
PA5.GPIOParameters=GPIO_Label
PA5.GPIO_Label=STM32_DAC_Y
PA5.Signal=COMP_DAC2_group
PB10.GPIOParameters=PinState,GPIO_Label,GPIO_ModeDefaultOutputPP
PB10.GPIO_Label=DAC_CLR
PB10.GPIO_ModeDefaultOutputPP=GPIO_MODE_OUTPUT_OD
PB10.PinState=GPIO_PIN_SET
PB10.Signal=GPIO_Output
PB11.GPIOParameters=GPIO_PuPd,GPIO_Label
PB11.GPIO_Label=DAC_IRQ
PB11.GPIO_PuPd=GPIO_NOPULL
PB11.Signal=GPXTI11
PB12.GPIOParameters=PinState,GPIO_Label,GPIO_ModeDefaultOutputPP
PB12.GPIO_Label=SPI2_CS
PB12.GPIO_ModeDefaultOutputPP=GPIO_MODE_OUTPUT_OD
PB12.PinState=GPIO_PIN_SET
PB12.Signal=GPIO_Output
PB13.Mode=Full_Duplex_Master
PB13.Signal=SPI2_SCK
PB14.Mode=Full_Duplex_Master
PB14.Signal=SPI2_MISO
PB15.Mode=Full_Duplex_Master
PB15.Signal=SPI2_MOSI
PB2.GPIOParameters=PinState,GPIO_Label,GPIO_ModeDefaultOutputPP
PB2.GPIO_Label=DAC_LDAC
PB2.GPIO_ModeDefaultOutputPP=GPIO_MODE_OUTPUT_OD
PB2.PinState=GPIO_PIN_SET
PB2.Signal=GPIO_Output
PB5.Mode=SYS_WakeUp5
PB5.Signal=SYS_WKUP6
PC9.GPIOParameters=PinState,GPIO_Label
PC9.GPIO_Label=DEBUG_LED
PC9.PinState=GPIO_PIN_SET
PC9.Signal=GPIO_Output
PF0-OSC_IN.Mode=HSE-External-Oscillator
PF0-OSC_IN.Signal=RCC_OSC_IN
PF1-OSC_OUT.Mode=HSE-External-Oscillator
PF1-OSC_OUT.Signal=RCC_OSC_OUT
RCC.SYSCLKFreq_VALUE=48000000
RCC.SYSCLKSource=RCC_SYSCLKSOURCE_PLLCLK
board=switchmod_code

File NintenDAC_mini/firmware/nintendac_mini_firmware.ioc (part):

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Mcu.Name=STM32F072C(8-B)Tx
Mcu.Package=LQFP48
Mcu.UserName=STM32F072C8Tx
PA11.Mode=Device
PA11.Signal=USB_DM
PA12.Mode=Device
PA12.Signal=USB_DP
PA13.Mode=Serial_Wire
PA13.Signal=SYS_SWDIO
PA14.Mode=Serial_Wire
PA14.Signal=SYS_SWCLK
PA4.Signal=COMP_DAC1_group
PA5.Signal=COMP_DAC2_group
PA8.GPIOParameters=GPIO_PuPd,GPIO_Label
PA8.GPIO_Label=USER_BUTTON
PA8.GPIO_PuPd=GPIO_PULLUP
PA8.Signal=GPIO_Input
PB10.Mode=I2C
PB10.Signal=I2C2_SCL
PB11.Mode=I2C
PB11.Signal=I2C2_SDA
PB15.GPIOParameters=GPIO_PuPd,GPIO_Label
PB15.GPIO_Label=USB_PRESENT
PB15.GPIO_PuPd=GPIO_PULLDOWN
PB15.Signal=GPIO_Input
PB7.GPIOParameters=GPIO_Label
PB7.GPIO_Label=DUP_BUTTON
PB7.Signal=GPIO_Output
PB8.GPIOParameters=GPIO_Speed,PinState,GPIO_Label,GPIO_ModeDefaultOutputPP
PB8.GPIO_Label=KEYPAD_COL1
PB8.GPIO_ModeDefaultOutputPP=GPIO_MODE_OUTPUT_OD
PB8.GPIO_Speed=GPIO_SPEED_FREQ_LOW
PB8.PinState=GPIO_PIN_SET
PB8.Signal=GPIO_Output
PC13.GPIOParameters=PinState,GPIO_Label
PC13.GPIO_Label=DEBUG_LED
PC13.PinState=GPIO_PIN_SET
PC13.Signal=GPIO_Output
PF0-OSC_IN.Mode=HSE-External-Oscillator
PF0-OSC_IN.Signal=RCC_OSC_IN
PF1-OSC_OUT.Mode=HSE-External-Oscillator
PF1-OSC_OUT.Signal=RCC_OSC_OUT
RCC.SYSCLKFreq_VALUE=48000000
RCC.SYSCLKSource=RCC_SYSCLKSOURCE_PLLCLK
board=nintendac_mini_firmware

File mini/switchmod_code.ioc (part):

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Mcu.Name=STM32F072C(8-B)Tx
Mcu.Package=LQFP48
Mcu.UserName=STM32F072C8Tx
PA11.Mode=Device
PA11.Signal=USB_DM
PA12.Mode=Device
PA12.Signal=USB_DP
PA13.Mode=Serial_Wire
PA13.Signal=SYS_SWDIO
PA14.Mode=Serial_Wire
PA14.Signal=SYS_SWCLK
PB10.Mode=I2C
PB10.Signal=I2C2_SCL
PB11.Mode=I2C
PB11.Signal=I2C2_SDA
PB6.Mode=I2C
PB6.Signal=I2C1_SCL
PB7.Mode=I2C
PB7.Signal=I2C1_SDA
PC14-OSC32_IN.Mode=LSE-External-Oscillator
PC14-OSC32_IN.Signal=RCC_OSC32_IN
PC15-OSC32_OUT.Mode=LSE-External-Oscillator
PC15-OSC32_OUT.Signal=RCC_OSC32_OUT
PF0-OSC_IN.Mode=HSE-External-Oscillator
PF0-OSC_IN.Signal=RCC_OSC_IN
PF1-OSC_OUT.Mode=HSE-External-Oscillator
PF1-OSC_OUT.Signal=RCC_OSC_OUT

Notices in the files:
parts and their libraries:
SparkFun-Passives: Licensing: Creative Commons ShareAlike 4.0 International - https://creativecommons.org/licenses/by-sa/4.0
